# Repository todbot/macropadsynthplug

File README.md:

# MacroPadSynthPlug!

Turn MacroPad RP2040's StemmaQT port into Audio Out + MIDI In

Demo video on Youtube:

## What is this?

The [Adafruit MacroPad RP2040](https://learn.adafruit.com/adafruit-macropad-rp2040/overview)
is really fun and could be a great musical instrument,
with its 12 keys, rotary encoder, OLED display, RP2040 chip, and 8MB of flash storage.

If it only had a way to get MIDI into it and Audio out of it!
Well now you can, with MacroPadSynthPlug!

MacroPadSynthPlug is a small board that plugs into a StemmaQT / Qwiic port
and gives you [TRS-A MIDI In](https://minimidi.world/) and Audio line out.
It's not I2C, but is using those pins. 

The MacroPad RP2040 can now be a stand-alone MIDI synth!

Examples provided for both [CircuitPython](https://circuitpython.org/) and [Arduino](https://arduino-pico.readthedocs.io/en/latest/):

* __drum_machine__ - CircuitPython-based drum sequencer ([demo1](https://youtu.be/jMKC_18M17U),[demo2](https://youtu.be/bJwyUjxc6VM) )
* __dronesynth__ - Arduino Mozzi 12-oscillator drone synth ([demo](https://youtu.be/kLwP-vyvtLM))
* __remixer__ - CircuitPython-based song remixer ([source](https://github.com/todbot/macropadsynthplug/tree/main/circuitpython/remixer))
* __monosynth1__ - Arduino Mozzi 2-oscillator bass monosynth w/ resonant low-pass filter ([source](https://github.com/todbot/macropadsynthplug/tree/main/arduino/monosynth1))

## How?

The [Raspberry Pi RP2040 chip](https://www.raspberrypi.com/documentation/microcontrollers/rp2040.html)
on the MacroPad RP2040 is amazingly configurable.

Normally a port like the StemmaQT I2C port would only be usable as an I2C bus. 
With the MacroPad RP2040, the two StemmaQT pins have the possible functionality:

* MacroPad RP2040 StemmaQT SDA -- GP20 - UART1 TX - PWM2B
* MacroPad RP2040 StemmaQT SCL -- GP21 - UART1 RX - PWM2A

MacroPadSynthPlug is a simple combination of two circuits:

* For MIDI in: StemmaQT SCL has an optoisolator circuit and TRS MIDI In jack

* For PWM Audio Out: StemmaQT SDA has a PWM filtering circuit and Audio Out jack

This is an "abuse" of the StemmaQT port, as it's meant only for I2C devices.
But it's safe, will not damage other StemmaQT devices,
but it does mean you "lose" the StemmaQT port for its normal use with I2C.

## Does this work for other boards with StemmaQT?

Short answer: Yes, with caveats

* For audio out, any board that can do PWM on StemmaQT SDA can use the
  Audio Out side of MacroPadSynthPlug

* For MIDI In, any boards that can do UART In on StemmaQT SCL can do TRS MIDI input. 
  A "software serial" for TRS MIDI In may work, and of course USB MIDI In will 
  always work

This makes this list of boards this works with kinda small. 

### Tested boards:

* [Adafruit MacroPad RP2040](https://learn.adafruit.com/adafruit-macropad-rp2040)

* [Adadfruit KB2040 "Keeboar"](https://learn.adafruit.com/adafruit-kb2040)

* [Adafruit QTPy RP2040](https://learn.adafruit.com/adafruit-qt-py-2040) 
  * with a PIO-based UART libary like [`SerialPIO`](https://arduino-pico.readthedocs.io/en/latest/piouart.html) or [`adafruit_pio_uart`](https://github.com/adafruit/Adafruit_CircuitPython_PIO_UART)
  * as an example, see [qtpy_mpsp_synth](./circuitpython/qtpy_mpsp_synth/code.py)

* Raspberry Pi Pico or Pico 2 
  * with a [StemmaQT](https://www.adafruit.com/product/4209) / [Qwiic](https://www.sparkfun.com/flexible-qwiic-cable-breadboard-jumper-4-pin.html) breadboard jumper cable

## Why?

Seems like fun?  I have built many little hardware synths, like:

- [PicoStepSeq](https://github.com/todbot/picostepseq)
- [picotouchsynth](https://github.com/todbot/picotouchsynth)
- [plinkykeeb](https://github.com/todbot/plinkykeeb)
- [seeknobs](https://github.com/todbot/seeknobs)

and wanted the MacroPad RP2040 to join in the fun.

## Are these for sale?

Yes! [Get one now at Tindie!](https://www.tindie.com/products/todbot/macropadsynthplug-turn-rp2040-into-a-synth/)

## Action shots

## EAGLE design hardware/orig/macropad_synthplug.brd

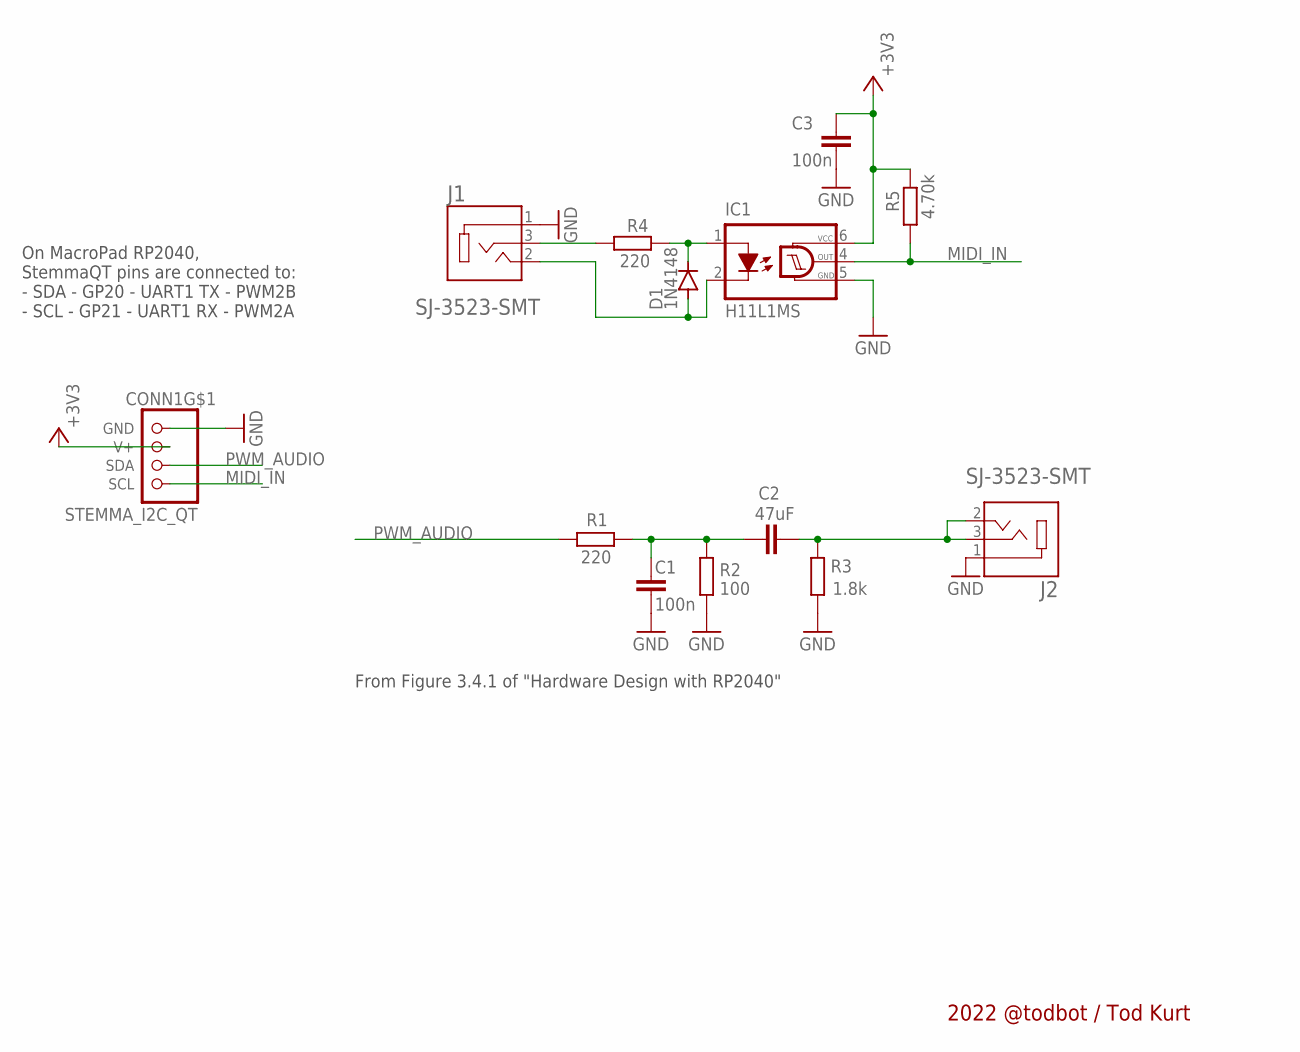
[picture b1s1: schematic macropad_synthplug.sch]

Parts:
C1, C3: 100n; C0805
C2: 47uF; C0805
CONN1: STEMMA_I2C_QT; JST_SH4
D1: 1N4148; SOD123
IC1: H11L1MS; DIL6-SMD
J1, J2: SJ-3523-SMT; CUI_SJ-3523-SMT
R1, R4: 220; R0805
R2: 100; R0805
R3: 1.8k; R0805
R5: 4.70k; R0805

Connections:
+3V3: C3.1, CONN1.2 (V+), IC1.6 (VCC), R5.1
GND: C1.2, C3.2, CONN1.1 (GND), IC1.5 (GND), J1.1, J2.1, R2.1, R3.2
MIDI_IN: CONN1.4 (SCL), IC1.4 (OUT), R5.2
unnamed: D1.C, IC1.1 (A), R4.1
unnamed: D1.A, IC1.2 (C), J1.2
unnamed: J1.3, R4.2
unnamed: C2.2, J2.2, J2.3, R3.1
unnamed: C1.1, C2.1, R1.1, R2.2
PWM_AUDIO: CONN1.3 (SDA), R1.2

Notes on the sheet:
On MacroPad RP2040, StemmaQT pins are connected to: - SDA - GP20 - UART1 TX - PWM2B - SCL - GP21 - UART1 RX - PWM2A
From Figure 3.4.1 of "Hardware Design with RP2040"
2022 @todbot / Tod Kurt

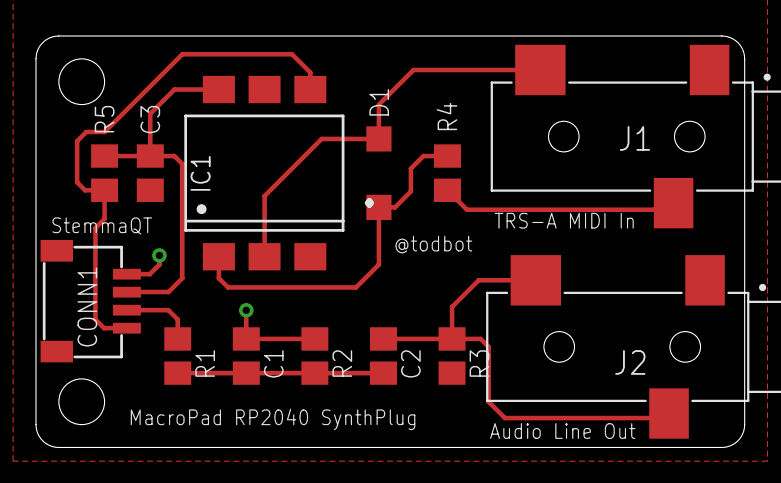
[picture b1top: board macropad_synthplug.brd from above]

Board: 2 copper layers, 39.4 x 22.9 mm, 15 parts (2 on the bottom side), 9 nets.

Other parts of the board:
U$1: VINTAGE_SATURN
U$2: VINTAGE_SPACESHIP_SM1

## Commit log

2022-12-15 submit!
2022-12-16 added some hardware test sketches
2022-12-31 add usb midi input to drummachine
2023-01-01 sync up with local
2023-01-01 add async attempt
2023-01-01 allow use of built-in tiny spkr
2023-01-01 added track mutes
2023-01-01 prelim pattern changing
2023-01-01 change display layout to be more usable
2023-01-01 cleanup
2023-01-01 sigh ticks overflow, why cant you be like arduino
2023-01-01 add docs images
2023-01-02 added sch pdf
2023-01-02 add ability to select multiple kits
2023-01-02 fix pattern for multi-kit setup
2023-01-02 display layout fix
2023-01-03 preparing for being abel to save patterns
2023-01-03 added kit2
2023-01-03 fix kit1_tac, prepare for save/load patterns
2023-01-03 mention about code_async, add boot.py for saving sequences
2023-01-05 add a kind of quantizing
2023-01-05 add patterns save/load first cut
2023-01-05 long version of board
2023-01-08 submit long version to fab
2023-01-08 cleanup arduino hardware test 1
2023-01-11 rework pattern storage, now using bit positions
2023-01-11 more UI improvements to drum_machine
2023-01-11 go back to arrays for sequence, but store as binary string
2023-01-12 save pattern cleanup
2023-01-12 clean up drumpatterns
2023-01-13 invert patterns data structure to make it easier to read and design demo patterns
2023-01-14 copy pattern and save pattern
2023-01-16 midi receive uses todbot_smolishmidi now
2023-01-16 crap
2023-01-21 get the trrs pinout right for realsies yeesh
2023-01-21 arduino tests rename
2023-01-21 sorta working hagiwo_additive_vco
2023-01-21 additive vco knob works better
2023-01-23 add macropadsynthplug verison of dronesynth
2023-01-23 more dronesynth
2023-01-23 more dronesynth work, pretty neat now
2023-01-24 dronesynth first midi
2023-01-24 dronesynth pretty fun now
2023-01-27 monosynth1 mostly works
2023-02-02 oops on additive_vco_synth
2023-02-03 tindie link
2023-02-12 oops forgot drum_display.py
2023-03-02 add autopunkconsole
2023-03-09 cleanup silkscreen, send to fab
2023-03-19 circuitpython drum_machine: how did I miss this
2023-10-23 arduino/dronesynth, fix serial midi input, issue #1
2023-10-23 arduino/dronesynth: handle noteon/noteoff better
2023-10-23 arduino/monosynth1: fix serial MIDI in
2024-09-29 clarify what StemmaQT pins do what on MacroPad RP2040
2024-10-22 new synthplug incoming
2024-10-22 sch reorg
2024-10-22 mk2 size and silkscreen update
2024-10-22 mk2 routing fixes
2024-10-30 silkscreen for mk2
2024-11-23 mk2 silkscreen update
2025-05-16 readme updates
2025-05-16 qtpy rp2040 example
